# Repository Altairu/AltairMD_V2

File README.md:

# AltairMD_V2
モタドラver2.0
apin,bpin,pwm
ir2302

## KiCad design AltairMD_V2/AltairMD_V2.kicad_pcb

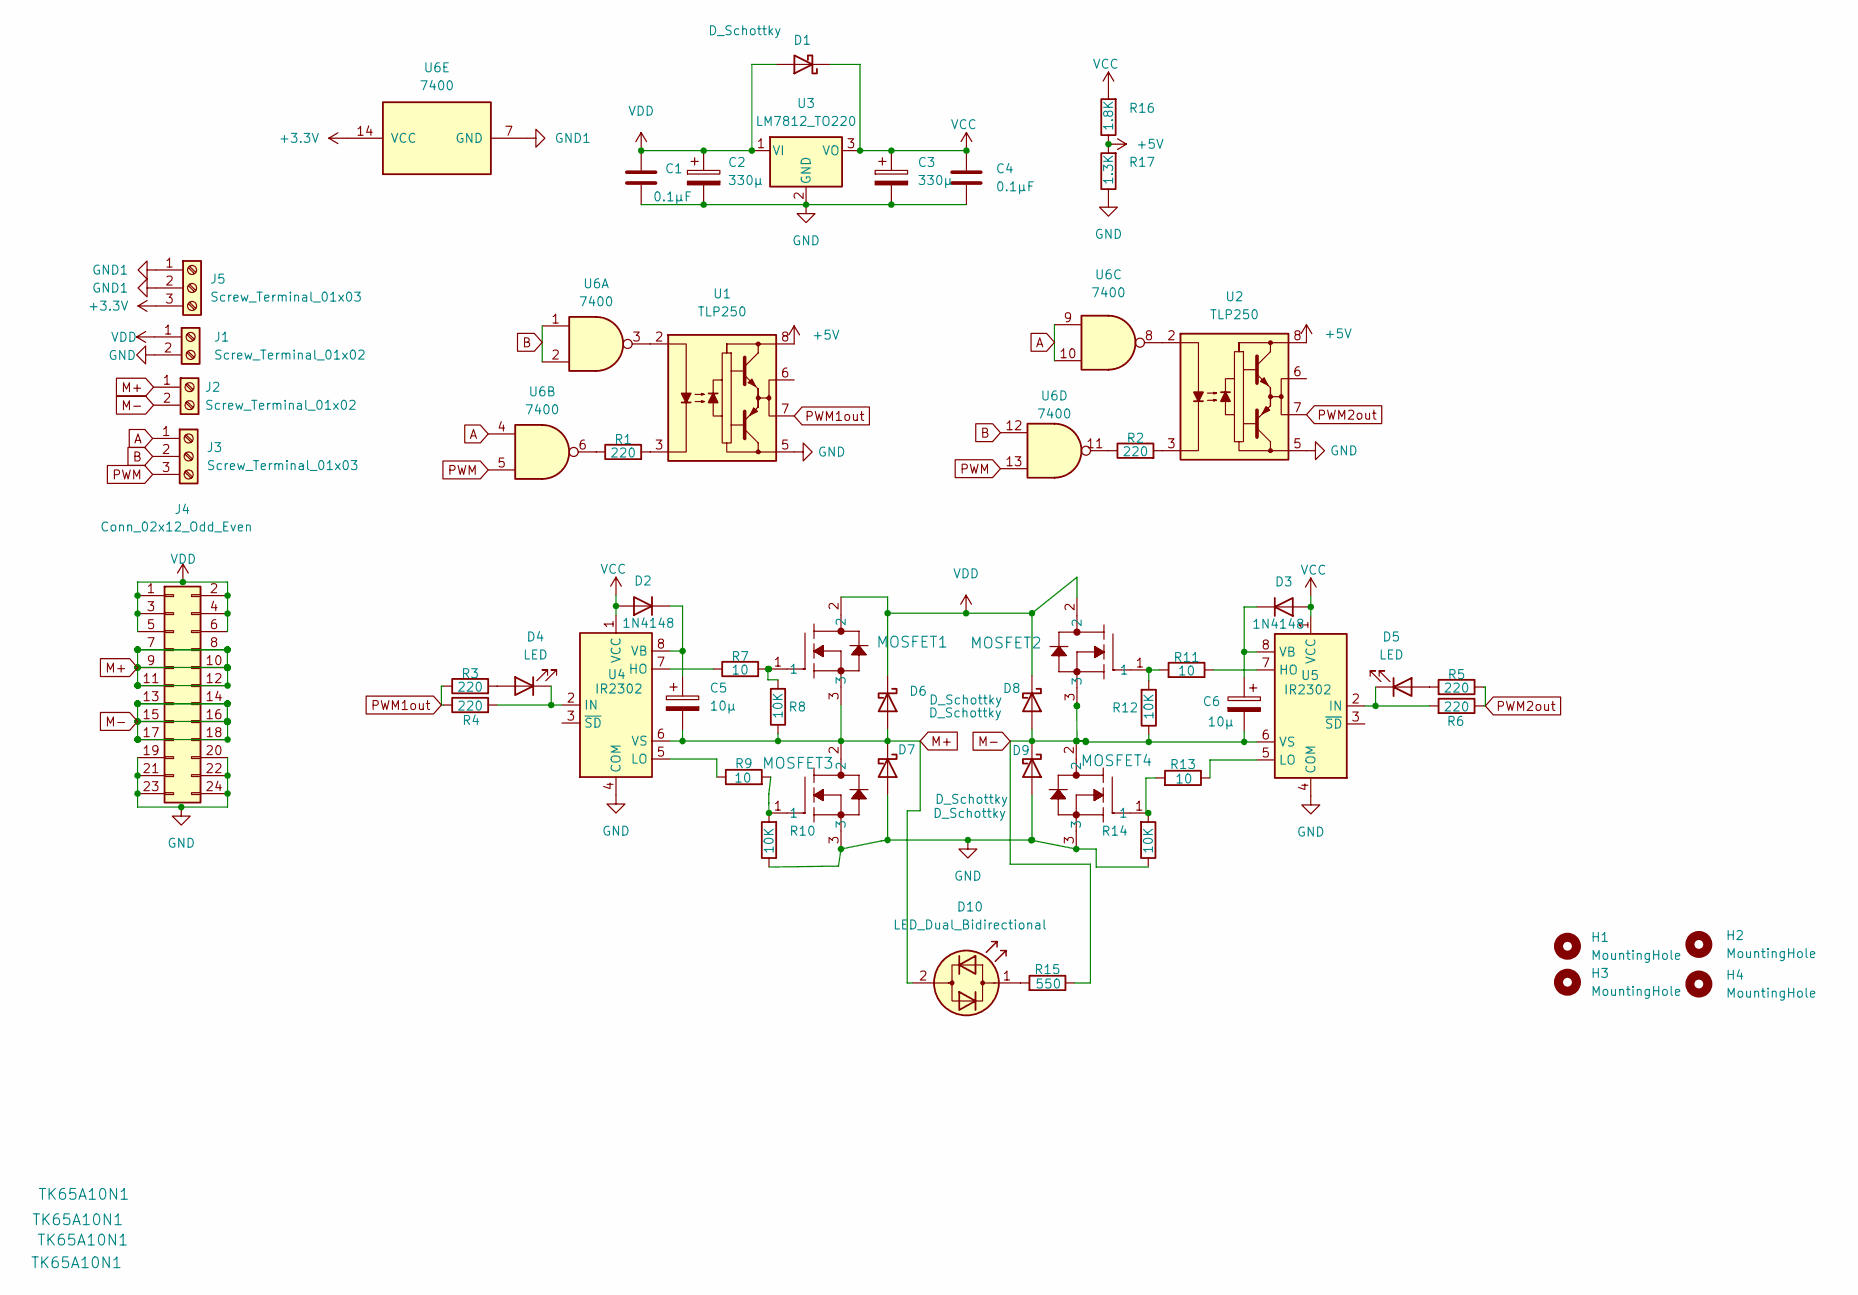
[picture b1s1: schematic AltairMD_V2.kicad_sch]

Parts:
C1, C4: 0.1μF; CP_Radial_Tantal_D9.0mm_P5.00mm
C2, C3: 330μ; CP_Radial_D10.0mm_P5.00mm
C5, C6: 10μ; CP_Radial_D5.0mm_P2.00mm
D1, D6, D7, D8, D9: D_Schottky; D_DO-35_SOD27_P10.16mm_Horizontal
D2, D3: 1N4148; D_DO-35_SOD27_P10.16mm_Horizontal
D4, D5: LED; LED_D3.0mm
D10: LED_Dual_Bidirectional; LED_D3.0mm
H1, H2, H3, H4: MountingHole; MountingHole_3.2mm_M3
J1, J2: Screw_Terminal_01x02; TerminalBlock_Phoenix_MKDS-3-2-5.08_1x02_P5.08mm_Horizontal
J3, J5: Screw_Terminal_01x03; TerminalBlock_Phoenix_MKDS-3-3-5.08_1x03_P5.08mm_Horizontal
J4: Conn_02x12_Odd_Even; PinHeader_2x12_P2.54mm_Horizontal
MOSFET1, MOSFET2, MOSFET3, MOSFET4: TK65A10N1; TO-220SIS_TOS
R1, R2, R3, R4, R5, R6: 220; R_Axial_DIN0207_L6.3mm_D2.5mm_P10.16mm_Horizontal
R7, R9, R11, R13: 10; R_Axial_DIN0207_L6.3mm_D2.5mm_P10.16mm_Horizontal
R8, R10, R12, R14: 10K; R_Axial_DIN0207_L6.3mm_D2.5mm_P10.16mm_Horizontal
R15: 550; R_Axial_DIN0207_L6.3mm_D2.5mm_P10.16mm_Horizontal
R16: 1.8K; R_Axial_DIN0207_L6.3mm_D2.5mm_P10.16mm_Horizontal
R17: 1.3K; R_Axial_DIN0207_L6.3mm_D2.5mm_P10.16mm_Horizontal
U1, U2: TLP250; DIP-8_W7.62mm
U3: LM7812_TO220; TO-220-3_Vertical
U4, U5: IR2302; DIP-8_W7.62mm
U6: 7400; DIP-14_W7.62mm

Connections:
+3.3V: J5.3, U6.14 (VCC)
+5V: R16.1, R17.2, U1.8 (VCC), U2.8 (VCC)
A: J3.1, U6.4, U6.9, U6.10
B: J3.2, U6.1, U6.2, U6.12
GND: C1.2, C2.2, C3.2, C4.2, D7.2 (A), D9.2 (A), J1.2, J4.19, J4.20, J4.21, J4.22, J4.23, J4.24, MOSFET3.3, R10.1, R17.1, U1.5 (VEE), U2.5 (VEE), U3.2 (GND), U4.4 (COM), U5.4 (COM)
GND1: J5.1, J5.2, U6.7 (GND)
M+: C5.2, D6.2 (A), D7.1 (K), D10.2 (AK), J2.1, J4.7, J4.8, J4.9, J4.10, J4.11, J4.12, MOSFET1.3, MOSFET3.2, R8.1, U4.6 (VS)
M-: C6.2, D8.2 (A), D9.1 (K), J2.2, J4.13, J4.14, J4.15, J4.16, J4.17, J4.18, MOSFET2.3, MOSFET4.2, R12.1, R15.1, U5.6 (VS)
unnamed: C5.1, D2.1 (K), U4.8 (VB)
unnamed: C6.1, D3.1 (K), U5.8 (VB)
unnamed: D4.1 (K), R4.2, U4.2 (IN)
unnamed: D4.2 (A), R3.2
unnamed: D5.1 (K), R6.2, U5.2 (IN)
unnamed: D5.2 (A), R5.2
unnamed: D10.1 (KA), R15.2
unnamed: MOSFET1.1, R7.2, R8.2
unnamed: MOSFET2.1, R11.2, R12.2
unnamed: MOSFET3.1, R9.2, R10.2
unnamed: MOSFET4.1, R13.2, R14.2
unnamed: MOSFET4.3, R14.1
unnamed: R1.1, U6.6
unnamed: R1.2, U1.3 (C)
unnamed: R2.1, U6.11
unnamed: R2.2, U2.3 (C)
unnamed: R7.1, U4.7 (HO)
unnamed: R9.1, U4.5 (LO)
unnamed: R11.1, U5.7 (HO)
unnamed: R13.1, U5.5 (LO)
unnamed: U1.2 (A), U6.3
unnamed: U2.2 (A), U6.8
PWM: J3.3, U6.5, U6.13
PWM1out: R3.1, R4.1, U1.7 (VO)
PWM2out: R5.1, R6.1, U2.7 (VO)
VCC: C3.1, C4.1, D1.1 (K), D2.2 (A), D3.2 (A), R16.2, U3.3 (VO), U4.1 (VCC), U5.1 (VCC)
VDD: C1.1, C2.1, D1.2 (A), D6.1 (K), D8.1 (K), J1.1, J4.1, J4.2, J4.3, J4.4, J4.5, J4.6, MOSFET1.2, MOSFET2.2, U3.1 (VI)

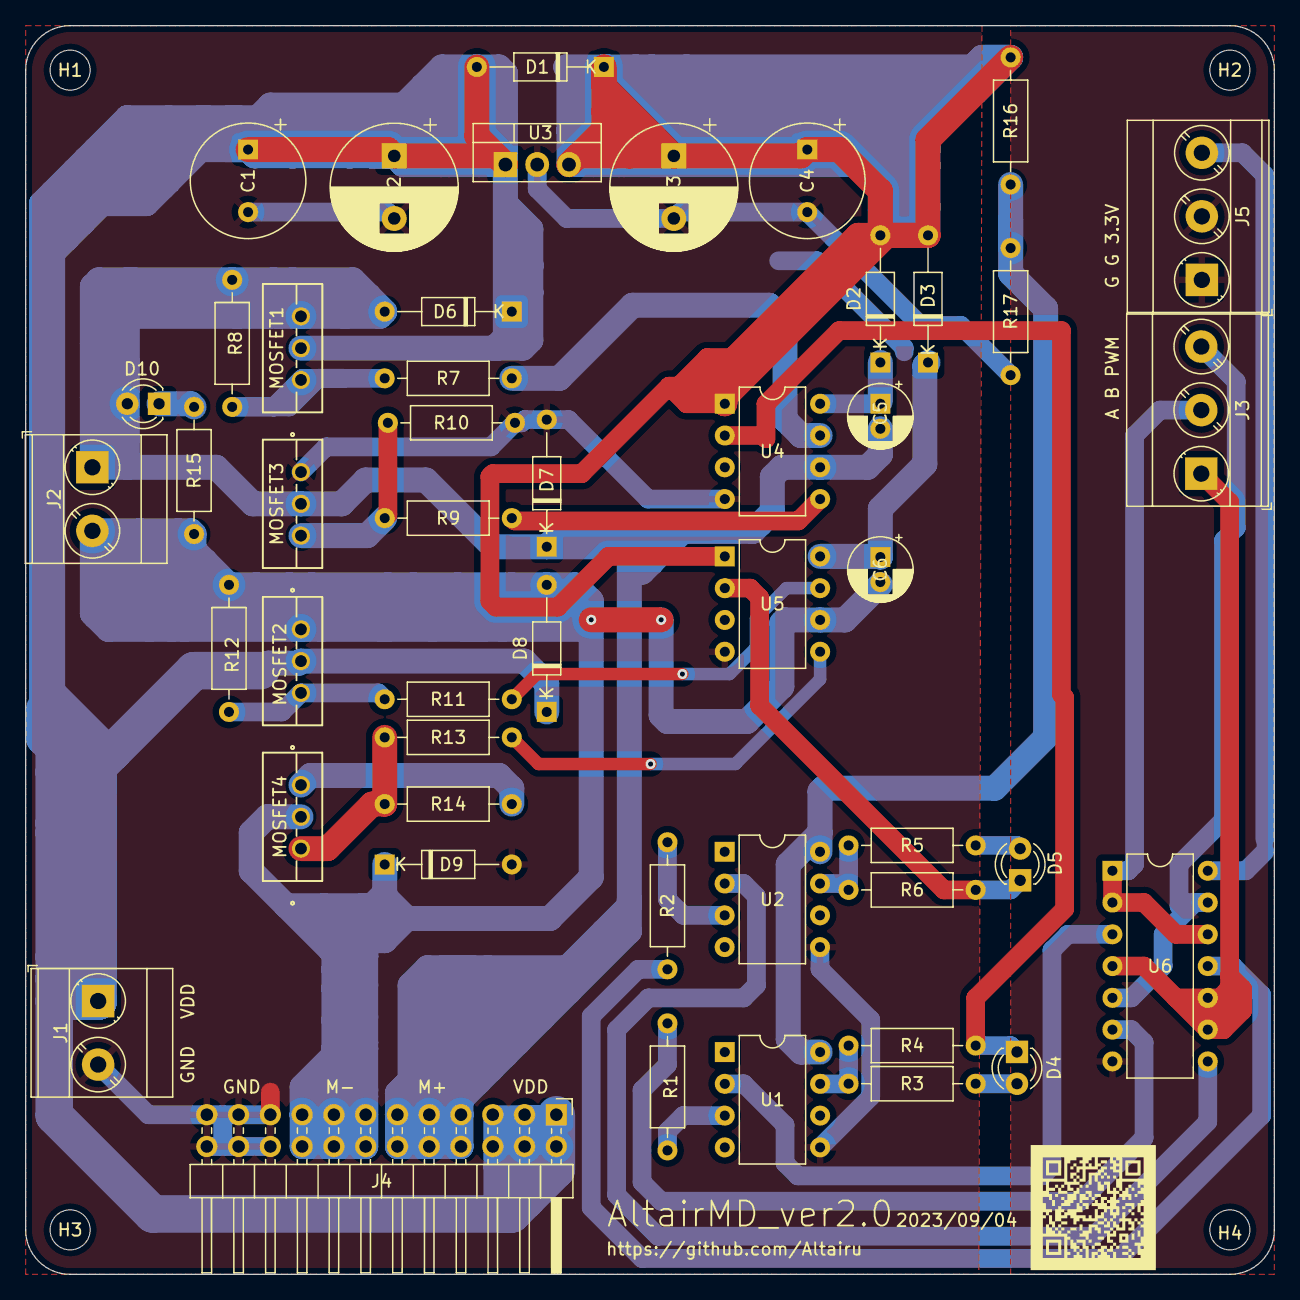
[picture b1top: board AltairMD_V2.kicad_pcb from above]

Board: 2 copper layers, 99.8 x 99.8 mm, 52 parts (0 on the bottom side), 35 nets.

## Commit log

2023-09-05 new モタドラ
